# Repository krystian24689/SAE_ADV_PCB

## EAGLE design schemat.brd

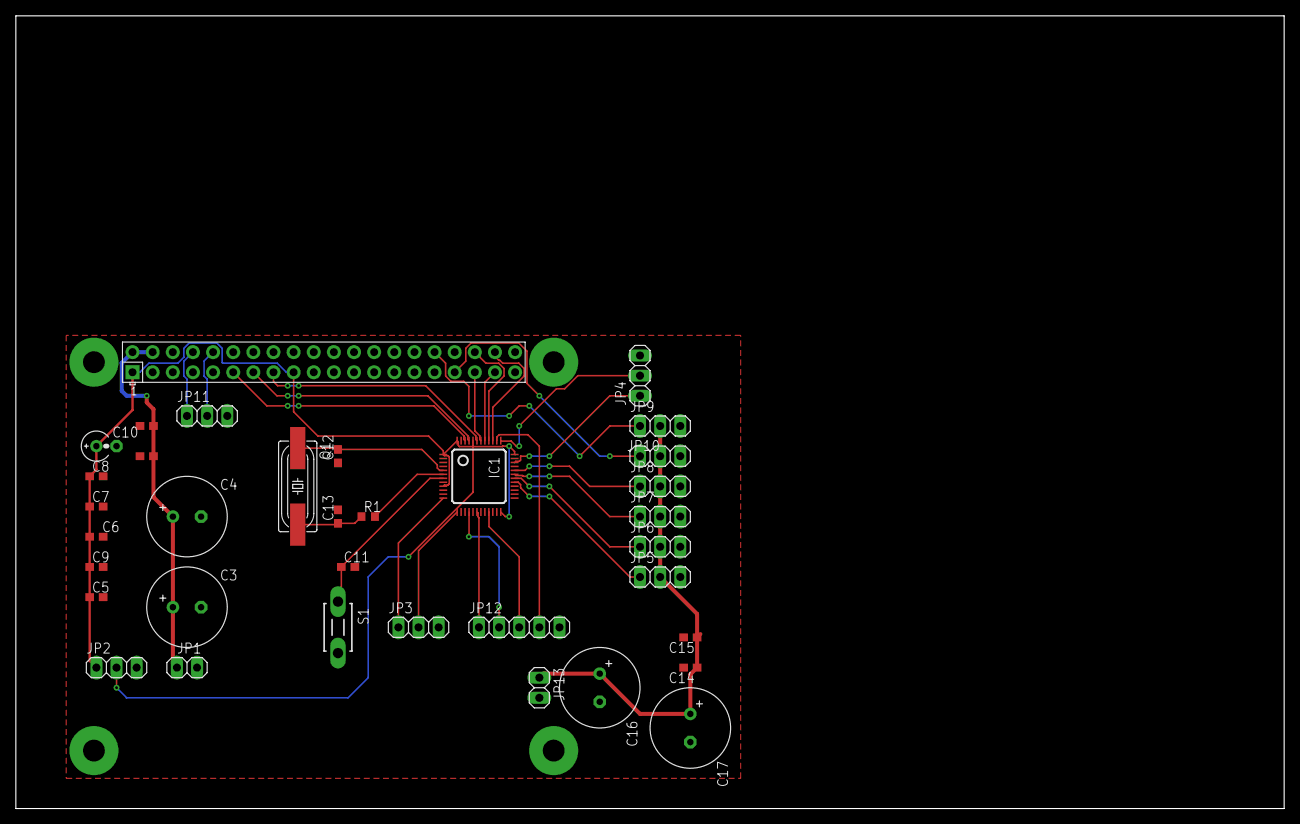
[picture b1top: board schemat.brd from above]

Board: 2 copper layers, 160.0 x 100.0 mm, 35 parts (0 on the bottom side), 32 nets.

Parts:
C1, C2, C5, C6, C7, C8, C9, C11, C14, C15: 100nF; C0603
C3, C4, C16, C17: 330uF; E3,5-10
C10: 4,7uF; E2,5RE
C12, C13: 10pF; C0603
IC1: STM32F10XCXT6; TQFP48
JP1, JP13: 1X02
JP2, JP3, JP4, JP5, JP6, JP7, JP8, JP9, JP10, JP11: 1X03
JP12: 1X05
Q1: HC49UP
R1: 2k; R0603
S1: DTS-3
X1: RASPI_BOARD_B+#_E4P; RASPI_BOARD_B+_EDGES_4DRILL_PAD

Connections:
+3V3: C5.1, C6.1, C7.1, C8.1, C9.1, C10.+, IC1.1, IC1.9, IC1.24, IC1.36, IC1.48, JP2.1, X1.1, X1.17
+5V: C1.1, C2.1, C3.+, C4.+, JP1.1, X1.2, X1.4
+5V_SERWO: C14.1, C15.1, C16.+, C17.+, JP5.2, JP6.2, JP7.2, JP8.2, JP9.2, JP10.2, JP13.1
BOOT_0: IC1.44, JP2.2
GND: C1.2, C2.2, C3.-, C4.-, C5.2, C6.2, C7.2, C8.2, C9.2, C10.-, C11.2, C12.1, C13.2, C14.2, C15.2, C16.-, C17.-, IC1.8, IC1.23, IC1.35, IC1.47, JP1.2, JP2.3, JP3.3, JP4.3, JP5.3, JP6.3, JP7.3, JP8.3, JP9.3, JP10.3, JP11.3, JP12.5, JP13.2, S1.2, X1.6, X1.9, X1.14, X1.20, X1.25, X1.30, X1.34, X1.39
NRST: C11.1, IC1.7, S1.1
OSC_IN: C12.2, IC1.5, Q1.1
OSC_OUT: IC1.6, R1.2
OSC_R: C13.1, Q1.2, R1.1
PWM_INPUT_1: IC1.18, JP12.1
PWM_INPUT_2: IC1.16, JP12.2
PWM_INPUT_3: IC1.21, JP12.3
PWM_INPUT_4: IC1.38, JP12.4
PWM_OUTPUT_0: JP9.1, X1.32
PWM_OUTPUT_1: JP10.1, X1.33
RPI_SIGNAL_1: IC1.42, X1.35
RPI_SIGNAL_2: IC1.41, X1.37
RPI_SIGNAL_3: IC1.40, X1.36
RPI_SIGNAL_4: IC1.39, X1.38
SERWO_PWM_OUTPUT_1: IC1.32, JP8.1
SERWO_PWM_OUTPUT_2: IC1.31, JP7.1
SERWO_PWM_OUTPUT_3: IC1.30, JP6.1
SERWO_PWM_OUTPUT_4: IC1.29, JP5.1
STM32_SIGNAL_1: IC1.46, X1.11
STM32_SIGNAL_2: IC1.45, X1.13
STM32_SIGNAL_3: IC1.43, X1.15
SWCLK: IC1.37, JP4.2
SWDIO: IC1.34, JP4.1
UART_RX: IC1.13, JP3.2
UART_RXD: JP11.2, X1.10
UART_TX: IC1.12, JP3.1
UART_TXD: JP11.1, X1.8

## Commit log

2019-12-10 podstawy
2019-12-12 SKOŃCZONY SCHEMAT
2019-12-17 Create RAR PCB V1
2019-12-17 PCB V1
2019-12-18 SAE_ADV_PCB_V2
